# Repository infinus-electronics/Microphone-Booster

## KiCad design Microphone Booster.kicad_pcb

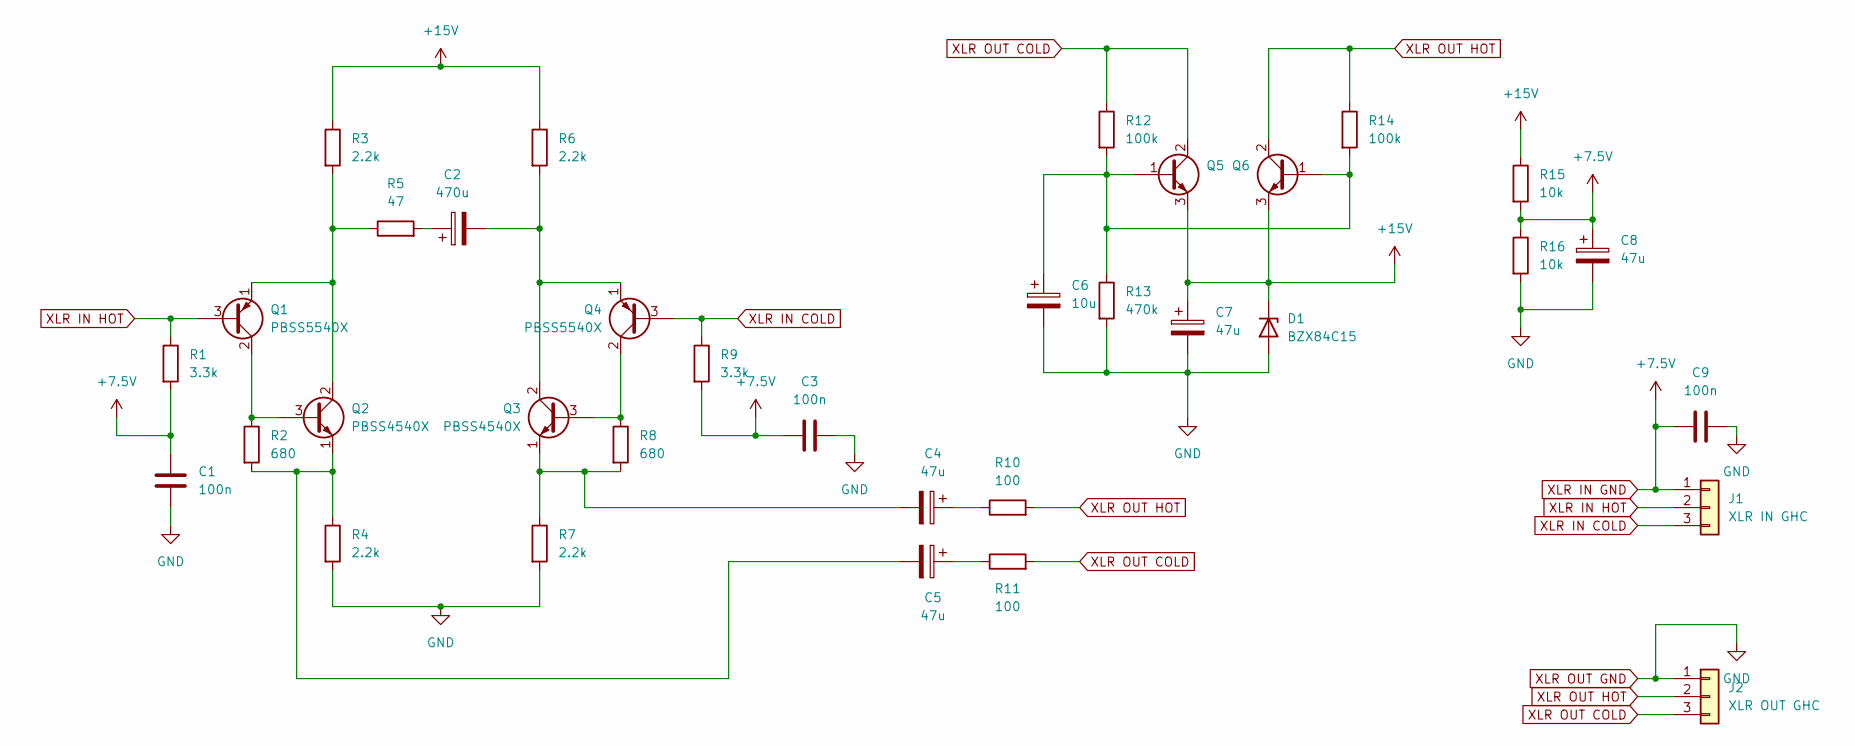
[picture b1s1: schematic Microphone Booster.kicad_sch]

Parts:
C1, C3, C9: 100n; C_0603_1608Metric_Pad1.08x0.95mm_HandSolder
C2: 470u; CP_Elec_10x10
C4, C5, C7, C8: 47u; CP_Elec_6.3x5.8
C6: 10u; CP_Elec_4x5.7
D1: BZX84C15; D_SOT-23_ANK
J1: XLR IN GHC; PinHeader_1x03_P2.54mm_Vertical
J2: XLR OUT GHC; PinHeader_1x03_P2.54mm_Vertical
Q1, Q4: PBSS5540X; SOT-89-3_Handsoldering
Q2, Q3: PBSS4540X; SOT-89-3_Handsoldering
Q5, Q6: MMBT3904; SOT-23_Handsoldering
R1, R9: 3.3k; R_0805_2012Metric_Pad1.20x1.40mm_HandSolder
R2, R8: 680; R_MELF_MMB-0207
R3, R4, R6, R7: 2.2k; R_0805_2012Metric_Pad1.20x1.40mm_HandSolder
R5: 47; R_0805_2012Metric_Pad1.20x1.40mm_HandSolder
R10, R11: 100; R_0805_2012Metric_Pad1.20x1.40mm_HandSolder
R12, R14: 100k; R_MELF_MMB-0207
R13: 470k; R_MELF_MMB-0207
R15, R16: 10k; R_MELF_MMB-0207

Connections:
+15V: C7.1, D1.1 (K), Q5.3 (E), Q6.3 (E), R3.1, R6.1, R15.1
unnamed: C2.1, R5.2
unnamed: C2.2, Q3.2 (C), Q4.1 (E), R6.2
unnamed: C4.1, R10.1
unnamed: C4.2, Q3.1 (E), R7.1, R8.2
unnamed: C5.1, R11.1
unnamed: C5.2, Q2.1 (E), R2.2, R4.1
unnamed: Q1.1 (E), Q2.2 (C), R3.2, R5.1
unnamed: Q1.2 (C), Q2.3 (B), R2.1
unnamed: Q3.3 (B), Q4.2 (C), R8.1
unnamed: C6.1, Q5.1 (B), Q6.1 (B), R12.2, R13.1, R14.2
XLR IN COLD: J1.3, Q4.3 (B), R9.1
XLR IN GND: C1.1, C3.2, C8.1, C9.1, J1.1, R1.2, R9.2, R15.2, R16.1
XLR IN HOT: J1.2, Q1.3 (B), R1.1
XLR OUT COLD: J2.3, Q5.2 (C), R11.2, R12.1
XLR OUT GND: C1.2, C3.1, C6.2, C7.2, C8.2, C9.2, D1.2 (A), J2.1, R4.2, R7.2, R13.2, R16.2
XLR OUT HOT: J2.2, Q6.2 (C), R10.2, R14.1

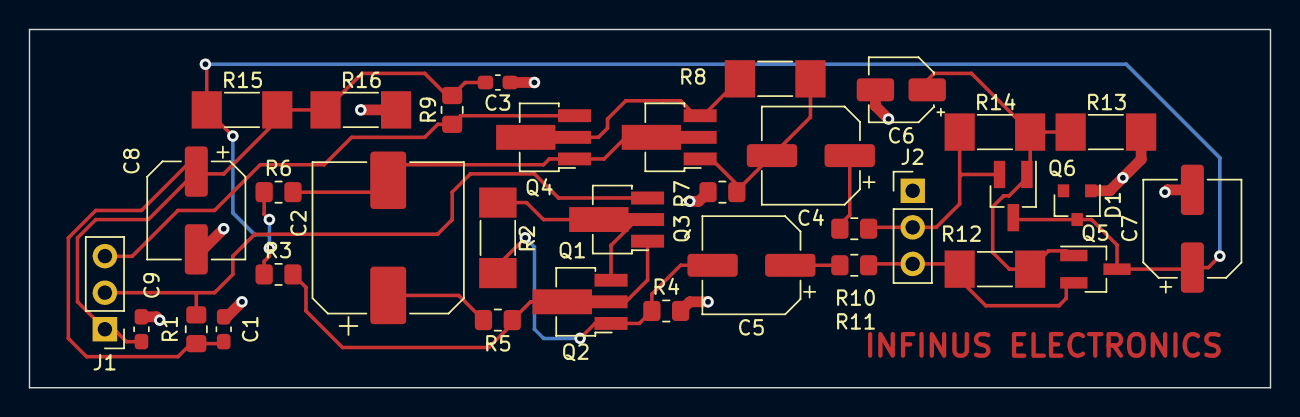
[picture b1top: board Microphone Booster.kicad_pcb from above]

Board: 2 copper layers, 86.2 x 24.9 mm, 34 parts (0 on the bottom side), 17 nets.
